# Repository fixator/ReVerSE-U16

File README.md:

# ReVerSE-U16
Development Kit

Плата ReVerSE-U16 ориентированна на создание SoC систем на микросхеме программируемой логики ПЛИС. Отлично подходит для домашнего обучения и позволяет полностью воссоздать множество ретро-компьютеров.
Для программирования используются программаторы и отладочные среды, позволяющие задать желаемую структуру цифрового устройства в виде принципиальной электрической схемы или программы на специальных языках описания аппаратуры: Verilog, VHDL, AHDL и др. В конфигурации ПЛИС реализуются почти все компоненты компьютера. Вне ПЛИС находятся только оперативная память, аппаратные интерфейсы для подключения клавиатуры, мыши, монитора, и других устройств.

#### Спецификация:
- FPGA Cyclone IV EP4CE22E22C7N (supports Cyclone III EP3C5/10/16/25, Cyclone IV EP4CE6/10/15/22)
- SDRAM 16MB x 16 bit (supports 4/16/32MB x 16 bit)
- SPI FLASH 64Mb (supports 64/16/1Mb)
- RTC DS1338Z + CR2032
- HDMI for sound and video (DVI or HDMI Male to VGA HD-15 15Pin Male Adapter Cable Cord)
- 10/100 Base-T Ethernet interface controller ENC424J600 with integrated MAC & PHY
- Dual USB 2.0 Host / Slave controller VNC2 (2 x ports)
- micro SD
- JTAG
- GPIO (uBUS)
- Power +5В 1A
- PCB Size 70 х 56 mm

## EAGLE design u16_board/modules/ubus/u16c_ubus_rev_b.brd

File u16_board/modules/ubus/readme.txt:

ReVerSE-U16 Adapter uBUS

09.06.2015	Rev.A Первая версия
16.09.2015	Rev.B Добавлены светодиоды LED1-8

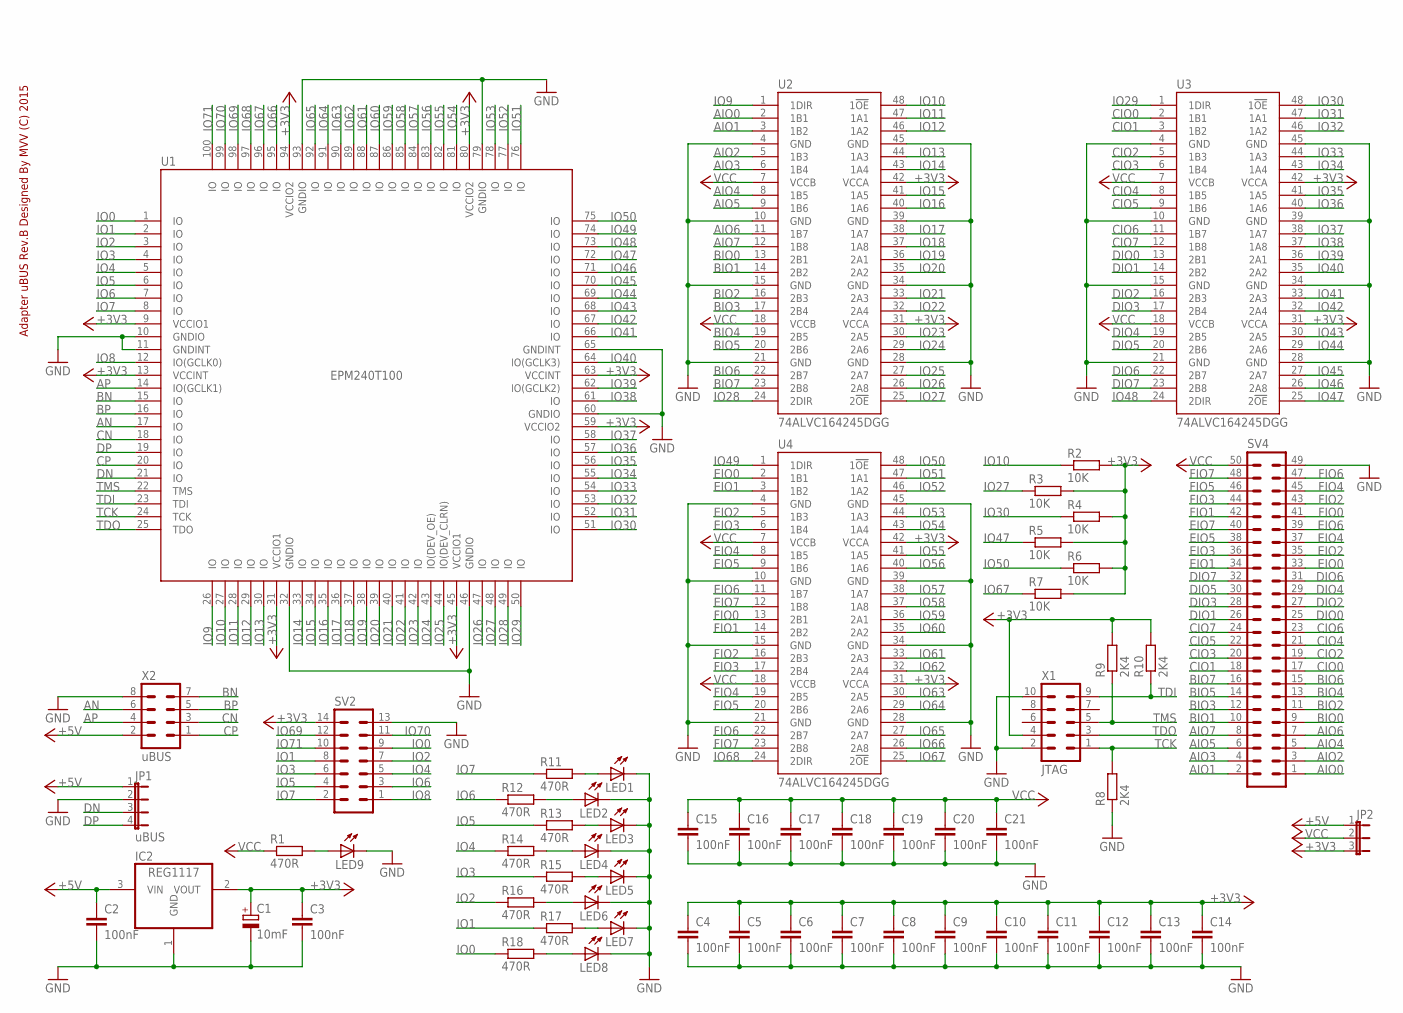
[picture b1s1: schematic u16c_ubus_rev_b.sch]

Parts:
C1: 10mF; CT6032
C2, C3, C4, C5, C6, C7, C8, C9, C10, C11, C12, C13, C14, C15, C16, C17, C18, C19, C20, C21: 100nF; C0805
IC2: REG1117; SOT223
JP1: uBUS; JP4
JP2: JP2E; JP2
LED1, LED2, LED3, LED4, LED5, LED6, LED7, LED8, LED9: LEDCHIPLED_0805; CHIPLED_0805
R1, R11, R12, R13, R14, R15, R16, R17, R18: 470R; R0805
R2, R3, R4, R5, R6, R7: 10K; R0805
R8, R9, R10: 2K4; R0805
SV2: ML14
SV4: ML50
U1: EPM240T100; TQFP100
U2, U3, U4: 74ALVC164245DGG; TSSOP48DGG
X1: JTAG; ML10
X2: uBUS; MA04-2

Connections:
+3V3: C1.+, C3.1, C4.1, C5.1, C6.1, C7.1, C8.1, C9.1, C10.1, C11.1, C12.1, C13.1, C14.1, IC2.2 (VOUT), JP2.3, R2.2, R3.2, R4.2, R5.2, R6.2, R7.2, R9.2, R10.2, SV2.14, U1.9 (VCCIO1), U1.13 (VCCINT), U1.31 (VCCIO1), U1.45 (VCCIO1), U1.59 (VCCIO2), U1.63 (VCCINT), U1.80 (VCCIO2), U1.94 (VCCIO2), U2.31 (VCCA), U2.42 (VCCA), U3.31 (VCCA), U3.42 (VCCA), U4.31 (VCCA), U4.42 (VCCA), X1.4
+5V: C2.1, IC2.3 (VIN), JP1.1, JP2.1, X2.2
AIO0: SV4.1, U2.2 (1B1)
AIO1: SV4.2, U2.3 (1B2)
AIO2: SV4.3, U2.5 (1B3)
AIO3: SV4.4, U2.6 (1B4)
AIO4: SV4.5, U2.8 (1B5)
AIO5: SV4.6, U2.9 (1B6)
AIO6: SV4.7, U2.11 (1B7)
AIO7: SV4.8, U2.12 (1B8)
AN: U1.17 (IO), X2.6
AP: U1.14 (IO(GCLK1)), X2.4
BIO0: SV4.9, U2.13 (2B1)
BIO1: SV4.10, U2.14 (2B2)
BIO2: SV4.11, U2.16 (2B3)
BIO3: SV4.12, U2.17 (2B4)
BIO4: SV4.13, U2.19 (2B5)
BIO5: SV4.14, U2.20 (2B6)
BIO6: SV4.15, U2.22 (2B7)
BIO7: SV4.16, U2.23 (2B8)
BN: U1.15 (IO), X2.7
BP: U1.16 (IO), X2.5
CIO0: SV4.17, U3.2 (1B1)
CIO1: SV4.18, U3.3 (1B2)
CIO2: SV4.19, U3.5 (1B3)
CIO3: SV4.20, U3.6 (1B4)
CIO4: SV4.21, U3.8 (1B5)
CIO5: SV4.22, U3.9 (1B6)
CIO6: SV4.23, U3.11 (1B7)
CIO7: SV4.24, U3.12 (1B8)
CN: U1.18 (IO), X2.3
CP: U1.20 (IO), X2.1
DIO0: SV4.25, U3.13 (2B1)
DIO1: SV4.26, U3.14 (2B2)
DIO2: SV4.27, U3.16 (2B3)
DIO3: SV4.28, U3.17 (2B4)
DIO4: SV4.29, U3.19 (2B5)
DIO5: SV4.30, U3.20 (2B6)
DIO6: SV4.31, U3.22 (2B7)
DIO7: SV4.32, U3.23 (2B8)
DN: JP1.3, U1.21 (IO)
DP: JP1.4, U1.19 (IO)
EIO0: SV4.33, U4.2 (1B1)
EIO1: SV4.34, U4.3 (1B2)
EIO2: SV4.35, U4.5 (1B3)
EIO3: SV4.36, U4.6 (1B4)
EIO4: SV4.37, U4.8 (1B5)
EIO5: SV4.38, U4.9 (1B6)
EIO6: SV4.39, U4.11 (1B7)
EIO7: SV4.40, U4.12 (1B8)
FIO0: SV4.41, U4.13 (2B1)
FIO1: SV4.42, U4.14 (2B2)
FIO2: SV4.43, U4.16 (2B3)
FIO3: SV4.44, U4.17 (2B4)
FIO4: SV4.45, U4.19 (2B5)
FIO5: SV4.46, U4.20 (2B6)
FIO6: SV4.47, U4.22 (2B7)
FIO7: SV4.48, U4.23 (2B8)
GND: C1.-, C2.2, C3.2, C4.2, C5.2, C6.2, C7.2, C8.2, C9.2, C10.2, C11.2, C12.2, C13.2, C14.2, C15.2, C16.2, C17.2, C18.2, C19.2, C20.2, C21.2, IC2.1 (GND), JP1.2, LED1.C, LED2.C, LED3.C, LED4.C, LED5.C, LED6.C, LED7.C, LED8.C, LED9.C, R8.1, SV2.13, SV4.49, U1.10 (GNDIO), U1.11 (GNDINT), U1.32 (GNDIO), U1.46 (GNDIO), U1.60 (GNDIO), U1.65 (GNDINT), U1.79 (GNDIO), U1.93 (GNDIO), U2.4 (GND), U2.10 (GND), U2.15 (GND), U2.21 (GND), U2.28 (GND), U2.34 (GND), U2.39 (GND), U2.45 (GND), U3.4 (GND), U3.10 (GND), U3.15 (GND), U3.21 (GND), U3.28 (GND), U3.34 (GND), U3.39 (GND), U3.45 (GND), U4.4 (GND), U4.10 (GND), U4.15 (GND), U4.21 (GND), U4.28 (GND), U4.34 (GND), U4.39 (GND), U4.45 (GND), X1.2, X1.10, X2.8
IO0: R18.1, SV2.9, U1.1 (IO)
IO1: R17.1, SV2.8, U1.2 (IO)
IO2: R16.1, SV2.7, U1.3 (IO)
IO3: R15.1, SV2.6, U1.4 (IO)
IO4: R14.1, SV2.5, U1.5 (IO)
IO5: R13.1, SV2.4, U1.6 (IO)
IO6: R12.1, SV2.3, U1.7 (IO)
IO7: R11.1, SV2.2, U1.8 (IO)
IO8: SV2.1, U1.12 (IO(GCLK0))
IO9: U1.26 (IO), U2.1 (1DIR)
IO10: R2.1, U1.27 (IO), U2.48 (1!OE)
IO11: U1.28 (IO), U2.47 (1A1)
IO12: U1.29 (IO), U2.46 (1A2)
IO13: U1.30 (IO), U2.44 (1A3)
IO14: U1.33 (IO), U2.43 (1A4)
IO15: U1.34 (IO), U2.41 (1A5)
IO16: U1.35 (IO), U2.40 (1A6)
IO17: U1.36 (IO), U2.38 (1A7)
IO18: U1.37 (IO), U2.37 (1A8)
IO19: U1.38 (IO), U2.36 (2A1)
IO20: U1.39 (IO), U2.35 (2A2)
IO21: U1.40 (IO), U2.33 (2A3)
IO22: U1.41 (IO), U2.32 (2A4)
IO23: U1.42 (IO), U2.30 (2A5)
IO24: U1.43 (IO(DEV_OE)), U2.29 (2A6)
IO25: U1.44 (IO(DEV_CLRN)), U2.27 (2A7)
IO26: U1.47 (IO), U2.26 (2A8)
IO27: R3.1, U1.48 (IO), U2.25 (2!OE)
IO28: U1.49 (IO), U2.24 (2DIR)
IO29: U1.50 (IO), U3.1 (1DIR)
IO30: R4.1, U1.51 (IO), U3.48 (1!OE)
IO31: U1.52 (IO), U3.47 (1A1)
IO32: U1.53 (IO), U3.46 (1A2)
IO33: U1.54 (IO), U3.44 (1A3)
IO34: U1.55 (IO), U3.43 (1A4)
IO35: U1.56 (IO), U3.41 (1A5)
IO36: U1.57 (IO), U3.40 (1A6)
IO37: U1.58 (IO), U3.38 (1A7)
IO38: U1.61 (IO), U3.37 (1A8)
IO39: U1.62 (IO(GCLK2)), U3.36 (2A1)
IO40: U1.64 (IO(GCLK3)), U3.35 (2A2)
IO41: U1.66 (IO), U3.33 (2A3)
IO42: U1.67 (IO), U3.32 (2A4)
IO43: U1.68 (IO), U3.30 (2A5)
IO44: U1.69 (IO), U3.29 (2A6)
IO45: U1.70 (IO), U3.27 (2A7)
IO46: U1.71 (IO), U3.26 (2A8)
IO47: R5.1, U1.72 (IO), U3.25 (2!OE)
IO48: U1.73 (IO), U3.24 (2DIR)
IO49: U1.74 (IO), U4.1 (1DIR)
IO50: R6.1, U1.75 (IO), U4.48 (1!OE)
IO51: U1.76 (IO), U4.47 (1A1)
IO52: U1.77 (IO), U4.46 (1A2)
IO53: U1.78 (IO), U4.44 (1A3)
IO54: U1.81 (IO), U4.43 (1A4)
IO55: U1.82 (IO), U4.41 (1A5)
IO56: U1.83 (IO), U4.40 (1A6)
IO57: U1.84 (IO), U4.38 (1A7)
IO58: U1.85 (IO), U4.37 (1A8)
IO59: U1.86 (IO), U4.36 (2A1)
IO60: U1.87 (IO), U4.35 (2A2)
IO61: U1.88 (IO), U4.33 (2A3)
IO62: U1.89 (IO), U4.32 (2A4)
IO63: U1.90 (IO), U4.30 (2A5)
IO64: U1.91 (IO), U4.29 (2A6)
IO65: U1.92 (IO), U4.27 (2A7)
IO66: U1.95 (IO), U4.26 (2A8)
IO67: R7.1, U1.96 (IO), U4.25 (2!OE)
IO68: U1.97 (IO), U4.24 (2DIR)
IO69: SV2.12, U1.98 (IO)
IO70: SV2.11, U1.99 (IO)
IO71: SV2.10, U1.100 (IO)
unnamed: LED1.A, R11.2
unnamed: LED2.A, R12.2
unnamed: LED3.A, R13.2
unnamed: LED4.A, R14.2
unnamed: LED5.A, R15.2
unnamed: LED6.A, R16.2
unnamed: LED7.A, R17.2
unnamed: LED8.A, R18.2
unnamed: LED9.A, R1.2
TCK: R8.2, U1.24 (TCK), X1.1
TDI: R10.1, U1.23 (TDI), X1.9
TDO: U1.25 (TDO), X1.3
TMS: R9.1, U1.22 (TMS), X1.5
VCC: C15.1, C16.1, C17.1, C18.1, C19.1, C20.1, C21.1, JP2.2, R1.1, SV4.50, U2.7 (VCCB), U2.18 (VCCB), U3.7 (VCCB), U3.18 (VCCB), U4.7 (VCCB), U4.18 (VCCB)

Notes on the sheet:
Adapter uBUS Rev.B Designed By MVV (C) 2015

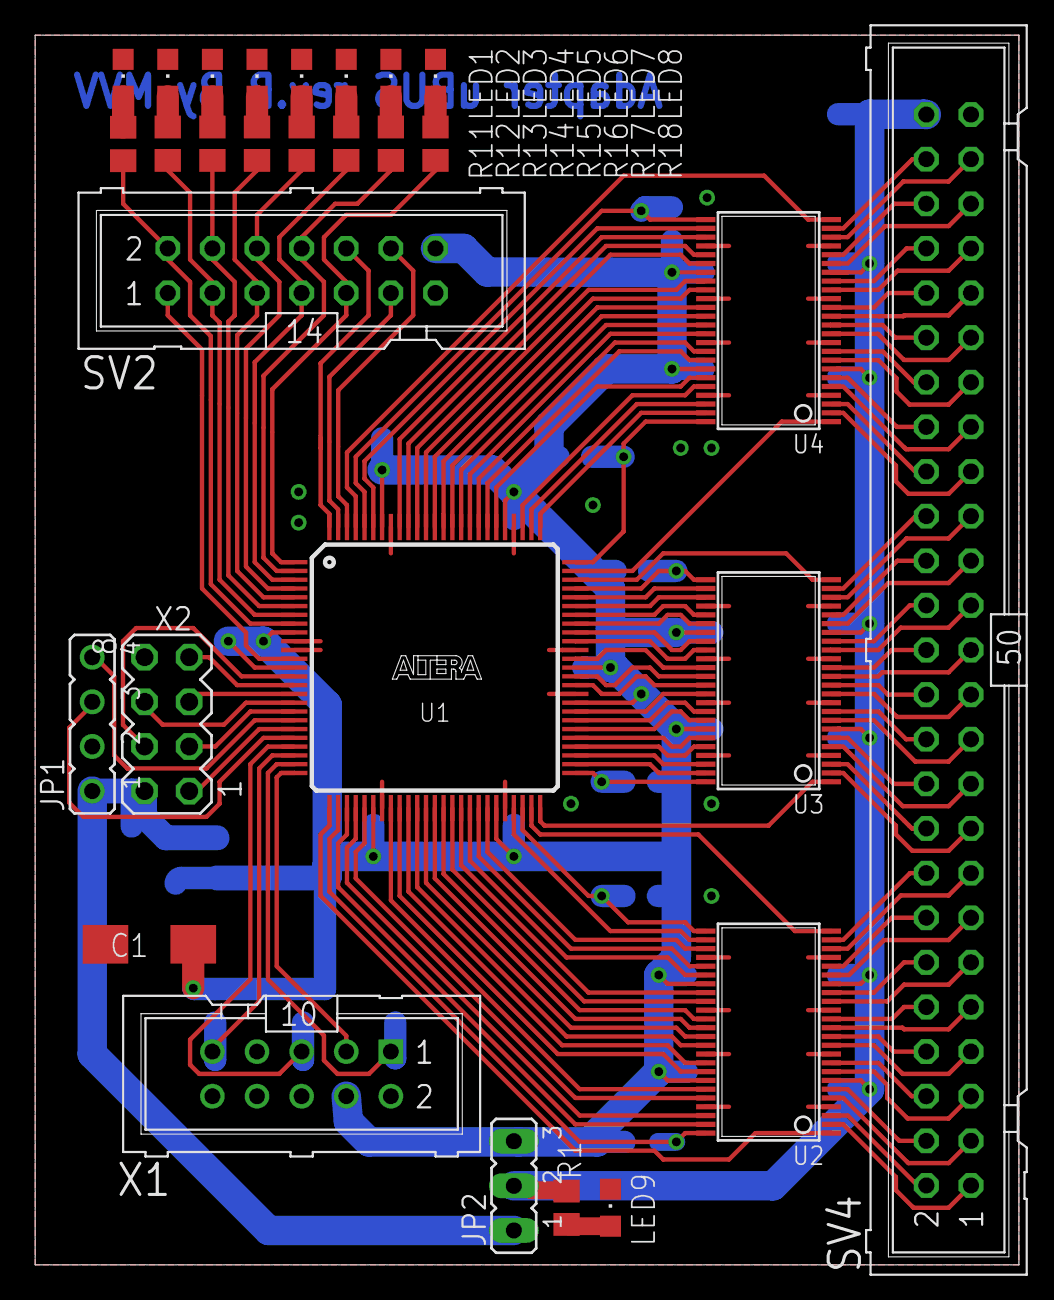
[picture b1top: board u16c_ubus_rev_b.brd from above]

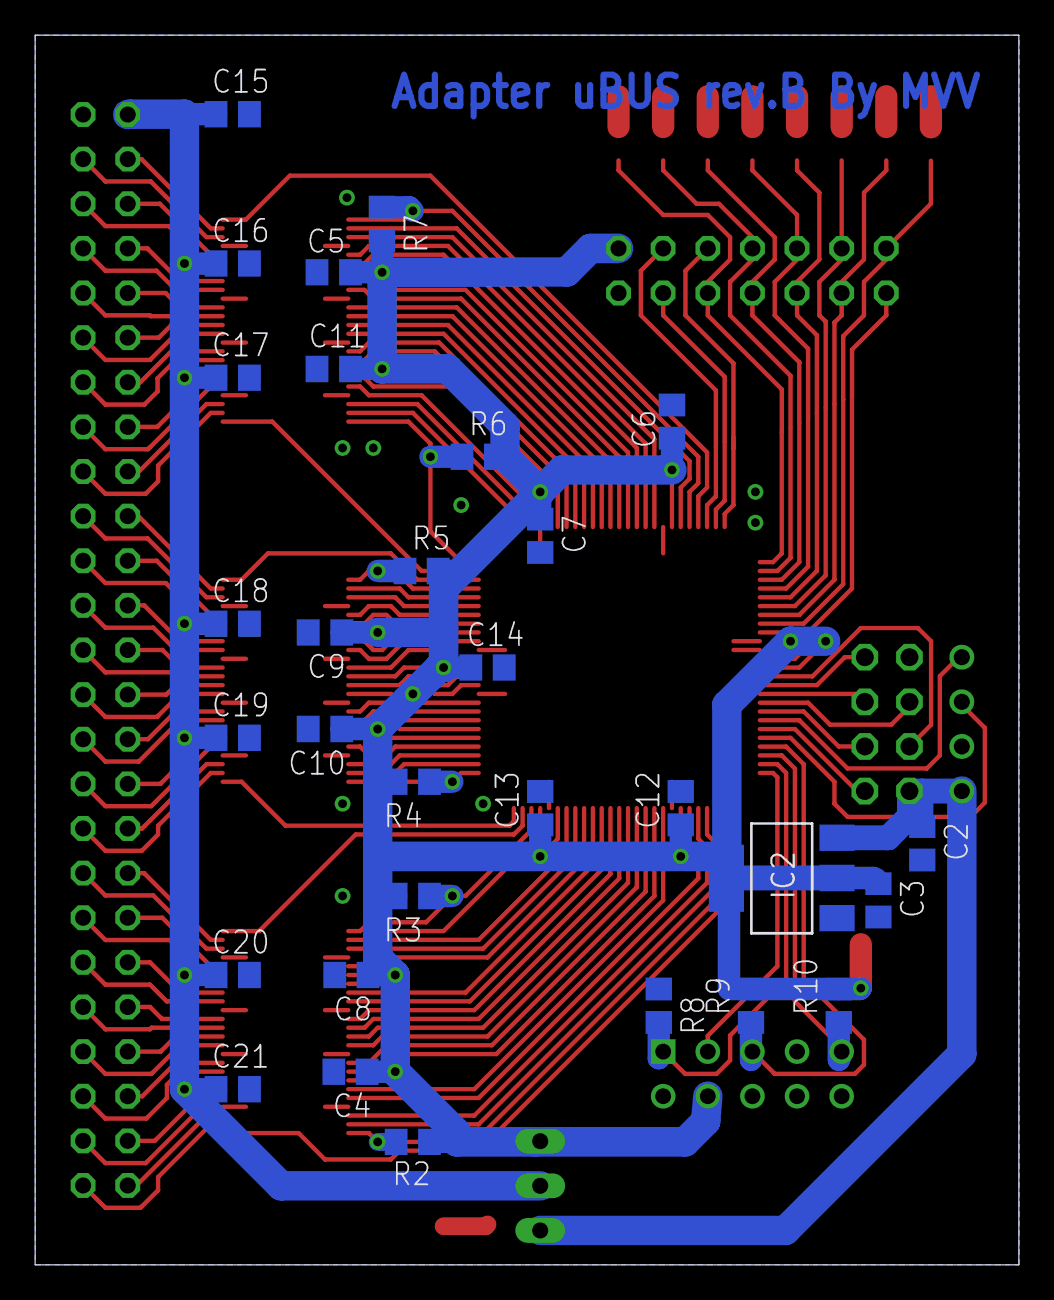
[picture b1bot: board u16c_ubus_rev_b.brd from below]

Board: 2 copper layers, 56.0 x 70.0 mm, 59 parts (30 on the bottom side), 145 nets.

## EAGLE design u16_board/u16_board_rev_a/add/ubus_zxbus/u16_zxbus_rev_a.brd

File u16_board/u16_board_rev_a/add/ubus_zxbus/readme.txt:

ReVerSE-U16 uBUS to ZX-Bus

09.06.2015	Rev.A Первая версия

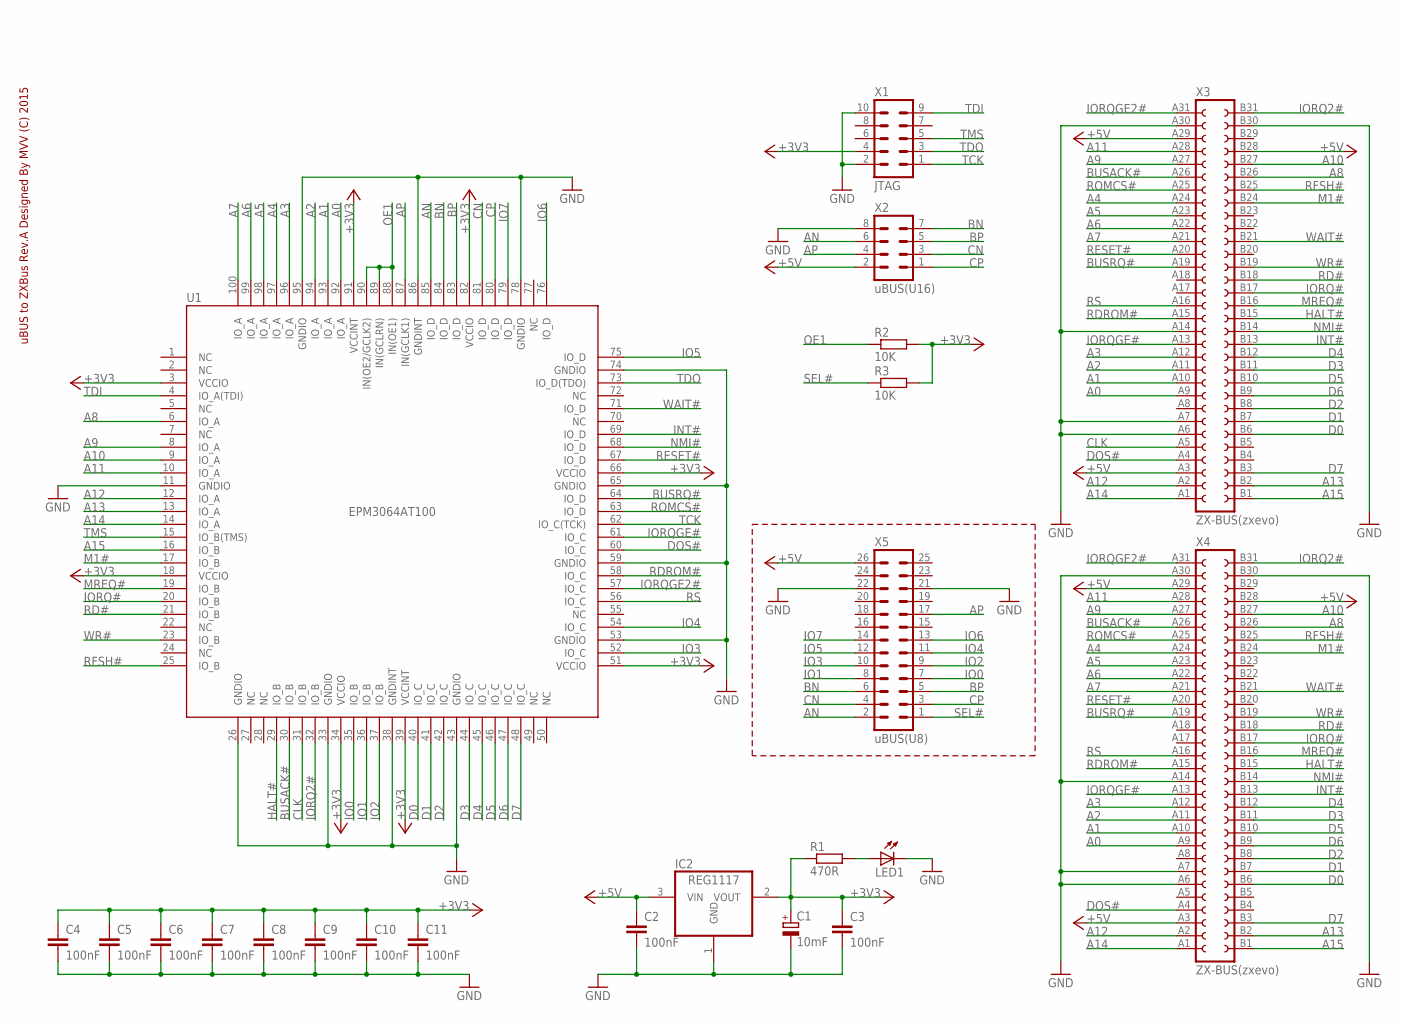
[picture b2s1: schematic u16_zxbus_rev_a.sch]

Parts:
C1: 10mF; CT6032
C2, C3, C4, C5, C6, C7, C8, C9, C10, C11: 100nF; C0805
IC2: REG1117; SOT223
LED1: LEDCHIPLED_0805; CHIPLED_0805
R1: 470R; R0805
R2, R3: 10K; R0805
U1: EPM3064AT100; TQFP100
X1: JTAG; ML10
X2: uBUS(U16); MA04-2
X3: ZX-BUS(zxevo); FE31-2
X4: ZX-BUS(zxevo); ESO3101
X5: uBUS(U8); ML26

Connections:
+3V3: C1.+, C3.1, C4.1, C5.1, C6.1, C7.1, C8.1, C9.1, C10.1, C11.1, IC2.2 (VOUT), R1.1, R2.2, R3.2, U1.3 (VCCIO), U1.18 (VCCIO), U1.34 (VCCIO), U1.39 (VCCINT), U1.51 (VCCIO), U1.66 (VCCIO), U1.82 (VCCIO), U1.91 (VCCINT), X1.4
+5V: C2.1, IC2.3 (VIN), X2.2, X3.A3, X3.A29, X3.B28, X4.A3, X4.A29, X4.B28, X5.26
A0: U1.92 (IO_A), X3.A9, X4.A9
A1: U1.93 (IO_A), X3.A10, X4.A10
A2: U1.94 (IO_A), X3.A11, X4.A11
A3: U1.96 (IO_A), X3.A12, X4.A12
A4: U1.97 (IO_A), X3.A24, X4.A24
A5: U1.98 (IO_A), X3.A23, X4.A23
A6: U1.99 (IO_A), X3.A22, X4.A22
A7: U1.100 (IO_A), X3.A21, X4.A21
A8: U1.6 (IO_A), X3.B26, X4.B26
A9: U1.8 (IO_A), X3.A27, X4.A27
A10: U1.9 (IO_A), X3.B27, X4.B27
A11: U1.10 (IO_A), X3.A28, X4.A28
A12: U1.12 (IO_A), X3.A2, X4.A2
A13: U1.13 (IO_A), X3.B2, X4.B2
A14: U1.14 (IO_A), X3.A1, X4.A1
A15: U1.16 (IO_B), X3.B1, X4.B1
AN: U1.85 (IO_D), X2.6, X5.2
AP: U1.87 (IN(GCLK1)), X2.4, X5.17
BN: U1.84 (IO_D), X2.7, X5.6
BP: U1.83 (IO_D), X2.5, X5.5
BUSACK#: U1.30 (IO_B), X3.A26, X4.A26
BUSRQ#: U1.64 (IO_D), X3.A19, X4.A19
CLK: U1.31 (IO_B), X3.A5
CN: U1.81 (IO_D), X2.3, X5.4
CP: U1.80 (IO_D), X2.1, X5.3
D0: U1.40 (IO_C), X3.B6, X4.B6
D1: U1.41 (IO_C), X3.B7, X4.B7
D2: U1.42 (IO_C), X3.B8, X4.B8
D3: U1.44 (IO_C), X3.B11, X4.B11
D4: U1.45 (IO_C), X3.B12, X4.B12
D5: U1.46 (IO_C), X3.B10, X4.B10
D6: U1.47 (IO_C), X3.B9, X4.B9
D7: U1.48 (IO_C), X3.B3, X4.B3
DOS#: U1.60 (IO_C), X3.A4, X4.A4
GND: C1.-, C2.2, C3.2, C4.2, C5.2, C6.2, C7.2, C8.2, C9.2, C10.2, C11.2, IC2.1 (GND), LED1.C, U1.11 (GNDIO), U1.26 (GNDIO), U1.33 (GNDIO), U1.38 (GNDINT), U1.43 (GNDIO), U1.53 (GNDIO), U1.59 (GNDIO), U1.65 (GNDIO), U1.74 (GNDIO), U1.78 (GNDIO), U1.86 (GNDINT), U1.95 (GNDIO), X1.2, X1.10, X2.8, X3.A6, X3.A7, X3.A14, X3.A30, X3.B30, X4.A6, X4.A7, X4.A14, X4.A30, X4.B30, X5.21, X5.22
HALT#: U1.29 (IO_B), X3.B15, X4.B15
INT#: U1.69 (IO_D), X3.B13, X4.B13
IO0: U1.35 (IO_B), X5.7
IO1: U1.36 (IO_B), X5.8
IO2: U1.37 (IO_B), X5.9
IO3: U1.52 (IO_C), X5.10
IO4: U1.54 (IO_C), X5.11
IO5: U1.75 (IO_D), X5.12
IO6: U1.76 (IO_D), X5.13
IO7: U1.79 (IO_D), X5.14
IORQ2#: U1.32 (IO_B), X3.B31, X4.B31
IORQ#: U1.20 (IO_B), X3.B17, X4.B17
IORQGE2#: U1.57 (IO_C), X3.A31, X4.A31
IORQGE#: U1.61 (IO_C), X3.A13, X4.A13
M1#: U1.17 (IO_B), X3.B24, X4.B24
MREQ#: U1.19 (IO_B), X3.B16, X4.B16
unnamed: LED1.A, R1.2
NMI#: U1.68 (IO_D), X3.B14, X4.B14
OE1: R2.1, U1.88 (IN(OE1)), U1.89 (IN(GCLRN)), U1.90 (IN(OE2/GCLK2))
RD#: U1.21 (IO_B), X3.B18, X4.B18
RDROM#: U1.58 (IO_C), X3.A15, X4.A15
RESET#: U1.67 (IO_D), X3.A20, X4.A20
RFSH#: U1.25 (IO_B), X3.B25, X4.B25
ROMCS#: U1.63 (IO_D), X3.A25, X4.A25
RS: U1.56 (IO_C), X3.A16, X4.A16
SEL#: R3.1, X5.1
TCK: U1.62 (IO_C(TCK)), X1.1
TDI: U1.4 (IO_A(TDI)), X1.9
TDO: U1.73 (IO_D(TDO)), X1.3
TMS: U1.15 (IO_B(TMS)), X1.5
WAIT#: U1.71 (IO_D), X3.B21, X4.B21
WR#: U1.23 (IO_B), X3.B19, X4.B19

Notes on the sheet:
uBUS to ZXBus Rev.A Designed By MVV (C) 2015

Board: 2 copper layers, 22 parts (0 on the bottom side), 69 nets, no tracks yet.

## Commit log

2015-03-21 Нет коментария
2015-03-21 Board
2015-03-21 Описание
2015-03-22 quad speccy demo
2015-03-22 Test
2015-03-24 loader
2015-03-25 Added images
2015-03-25 Добавлены Gerber файлы
2015-03-25 Исправления
2015-03-26 Добавил конфигурацию QuadSpeccy
2015-03-26 DMA-Sound
2015-04-01 USB Blaster
2015-04-01 V2Debug
2015-04-01 Speccy
2015-04-01 SoCZ80
2015-04-06 ZX-Poly
2015-04-10 Исправление в zint.v
2015-04-10 Добавлен jic
2015-05-13 zet added
2015-05-16 ZX-Spectrum 48K
2015-05-16 ZX-48K
2015-05-20 HDMI
2015-05-21 Обновление, доработана прошивка VNC2
2015-05-21 Deleted
2015-05-28 TO-DO EMS
2015-05-28 Added comment
2015-06-02 Добавлен ZX48K T80
2015-06-07 Добавлен zx128k
2015-06-09 uBUS to ZXBus
2015-06-09 readme to UTF8
2015-06-23 Audio Packets
2015-08-03 ReVerSE-U16 Rev.C
2015-08-06 Добавлен YM2413
2015-08-27 Добавил схему rev.c
2015-08-28 Added Atari800
2015-09-04 Atari800xl rev.20150904
2015-09-11 Modules
2015-09-11 Перенесено в modules
2015-09-11 Quad Speccy rev.20150911
2015-09-13 TS-Conf rev.20150912
2015-09-13 jic для EPCS16
2015-09-13 Quad Speccy build 20150912 for ReVerSE-U16 rev.A
2015-09-13 Удален jic для EPCS64
2015-09-13 TS-Conf build 20150912 for ReVerSE-U16 rev.A
2015-09-16 Adapter uBUS rev.B
2015-09-26 Добавил фото платы ReVerSE-U16 rev.C на EP3C10
2015-09-27 Фотографии прототипа
2015-09-27 Предыдущая версия прототипа
2015-09-27 Файлы для Eagle
2015-09-27 Вид платы прототипа
2015-09-27 Схема прототипа uBus Adapter rev.B
2015-10-13 Added Gerber files
2015-10-13 uBus-adapter rev.c
2015-10-22 Фото
2016-01-01 Quad Speccy build 20160101 for ReVerSE-U16 rev.C
2016-01-12 NES build 20160108 for ReVerSE-u16 rev.C
2016-01-26 Плата ReVerSE-U16 Rev.C в акриловом корпусе :)
2016-01-28 Update images
2016-02-17 NES build 20160217 for ReVerSE-U16 Rev.C
2016-02-17 Отладочный аудио модуль для платы ReVerSE-U16 Rev.C
2016-02-27 Радио-86РК build 20160227 for ReVerSE-U16 Rev.C
2016-03-13 NextZX (build 20160313) for ReVerSE-U16 Rev.C
2016-03-30 NextZX (build 20160230) for ReVerSE-U16 Rev.C
    nz80, deserializer, sdram
2016-04-17 Фото корпуса и комплекта
2016-04-17 Обновление описания
2016-06-11 HDMI Test
2016-06-12 hdmi test *.jic
    По просьбе vazman, добавлены jic файлы HDMI Test
2016-06-21 исправление в encoder
2016-06-21 Spec256 build 20160621 for ReVerSE-U16 rev.C
2016-06-21 HDMI Test build 20160621
2016-06-21 SPEC256 (build 20160621) for ReVerSE-U16 rev.C
2016-06-26 Исправленна работа дифпар TMDS
2016-06-26 Revert "Исправленна работа дифпар TMDS"
    This reverts commit 40f73a67a92e1aa9bee66c3c59f65bc482b77619.
2016-06-26 Atari800XL (build 20160626)
2016-06-26 Atari 800 XL (build 20160626)
2016-06-28 добавлена рамка
2016-07-15 Embedding YouTube Video in GitHub README
2016-07-15 Fixed README
2016-07-18 SPEC256 build 20160629
    HDMI Audio
2016-07-18 SPEC256 build 20160629 edit readme
    Edit readme
2016-07-22 NES build 20160722
    720x480@60Hz 24bpp, HDMI sound, framebuffer, palette 24bit
2016-07-23 NES (build 20160723)
    PLL clock, loader fixed
2016-08-13 NES build 20160813
2016-08-18 fixed, added string vos_iocell_set_config(26, 0, 0, 0, 1);
2016-08-19 SPEC256 build 20160819
2016-08-30 TS-Conf Build 20160830
    HDMI Audio 2Ch 48kHz, HID
2016-10-11 Empty Project
    Начните создание конфигурации
